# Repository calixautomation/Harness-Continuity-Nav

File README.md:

# LED Pattern Tester

A GUI application for testing wire connectivity on an 8x8 LED matrix. Uses a two-stage verification process: lock the wire in the slot, then verify connectivity by touching a metal plate.

## Quick Start

```bash
# Install dependencies
pip install -r harness_nav/requirements.txt

# Run the GUI (Desktop mode with test buttons)
cd HarnessNav
python harness_nav/scripts/run_desktop.py
```

## How It Works

```
┌─────────────────────────────────────────────────────────────┐
│                     LED Pattern Tester                       │
├──────────────┬──────────────────────────────────────────────┤
│              │                                              │
│  Pattern:    │    1   2   3   4   5   6   7   8            │
│  [Dropdown]  │                                              │
│              │    9  10  11  12  13  14  15  16            │
│  [Start]     │                                              │
│  [Reset]     │   17  18  19  20  21  22  23  24            │
│              │                                              │
│  [1. Lock]   │   25  26  27  28  29  30  31  32            │
│  [2. Verify] │                                              │
│              │   33  34  35  36  37  38  39  40            │
│  Progress:   │                                              │
│  ████░░ 50%  │   41  42  43  44  45  46  47  48            │
│              │                                              │
│  Current:    │   49  50  51  52  53  54  55  56            │
│  LED 4       │                                              │
│              │   57  58  59  60  61  62  63  64            │
│              │                                              │
└──────────────┴──────────────────────────────────────────────┘
```

### LED Colors

| Color | Meaning |
|-------|---------|
| Gray | Not part of pattern |
| Yellow | Needs to be tested |
| Cyan (blinking) | Currently active - waiting for wire |
| Orange | Wire locked in slot |
| Green | Verified/Passed |
| Red | Error/Wrong connection |

## Two-Stage Verification Workflow

```
1. Select Pattern    → LEDs in pattern turn YELLOW (pending)
2. Start Test        → First LED starts BLINKING (active)
3. Lock wire in slot → Limit switch triggers → LED turns ORANGE, beep (1500Hz)
4. Touch metal plate → Circuit completes → LED turns GREEN, beep (2500Hz)
5. Auto-advance      → Next LED starts blinking
6. Repeat            → Until all LEDs are GREEN
7. Complete          → Success message displayed
```

### Desktop Mode (Testing on PC)
- Use "1. Lock Wire" and "2. Verify Connection" buttons to simulate hardware
- Run with: `python harness_nav/scripts/run_desktop.py`

### Hardware Mode (Raspberry Pi)
- Buttons are hidden; uses SPI inputs
- Limit switch detects wire locked in slot
- Metal plate touch completes circuit for verification
- Run with: `python harness_nav/scripts/run_hardware.py`

## Creating Patterns

Use the built-in Pattern Editor (click "New Pattern") or edit `harness_nav/data/patterns.json`:

```json
{
    "patterns": [
        {
            "id": "pattern_1",
            "name": "Pattern 1",
            "description": "LEDs 3, 4, 8",
            "leds": [3, 4, 8]
        },
        {
            "id": "corners",
            "name": "Corner LEDs",
            "description": "All four corners",
            "leds": [1, 8, 57, 64]
        }
    ]
}
```

### LED Numbering

```
 1   2   3   4   5   6   7   8
 9  10  11  12  13  14  15  16
17  18  19  20  21  22  23  24
25  26  27  28  29  30  31  32
33  34  35  36  37  38  39  40
41  42  43  44  45  46  47  48
49  50  51  52  53  54  55  56
57  58  59  60  61  62  63  64
```

---

## Hardware Setup (Raspberry Pi)

### Required Components

| Component             | Description                               |
|-----------------------|-------------------------------------------|
| Raspberry Pi          | Main controller board                 |
| 10" Waveshare LCD     | Display for GUI (optional, can use HDMI)  |
| Limit Switch          | Detects when wire is locked in test slot  |
| Metal Plate           | Touch plate for connectivity verification |
| Piezo Buzzer          | Audio feedback (PWM driven)               |
| LEDs arranged in 8x8  | Physical LED display (optional)           |

### Wiring Diagram

```
Raspberry Pi 4B
       │
       ├── Pin 1 / 2 (3.3V / 5V) ──────── VCC (Pin 24 on TLC5925)
       │
       ├── Pin 6 / 9 (GND) ───────────── GND (Pin 12 on TLC5925)
       │
       ├── Pin 19 (GPIO 10 / MOSI) ───── SDI (Pin 23 on TLC5925)
       │
       ├── Pin 23 (GPIO 11 / SCLK) ───── CLK (Pin 22 on TLC5925)
       │
       ├── Pin 22 (GPIO 25) ──────────── LE (Pin 21 on TLC5925)
       │
       └── Pin 16 (GPIO 23) ──────────── \OE (Pin 10 on TLC5925, pulled LOW)
```

### Pin Connections

| Raspberry Pi Pin | TLC5925 Pin Name | TLC5925 Pin # | Notes                              |
|------------------|------------------|---------------|------------------------------------|
| Pin 1 / 2 (3.3V / 5V) | VCC              | Pin 24        | Logic power supply                |
| Pin 6 / 9 (GND)       | GND              | Pin 12        | Common ground                     |
| Pin 19 (GPIO 10 / MOSI)| SDI (Serial Data In) | Pin 23    | Data bus                          |
| Pin 23 (GPIO 11 / SCLK)| CLK (Clock)     | Pin 22        | Shift clock                       |
| Pin 22 (GPIO 25)       | LE (Latch Enable) | Pin 21      | Latches data into output          |
| Pin 16 (GPIO 23)       | \OE (Output Enable) | Pin 10   | Pull LOW (GND) to enable LED outputs |

### Circuit Notes

1. **Power Supply**: Connect the Raspberry Pi's 3.3V or 5V pin to the TLC5925's VCC (Pin 24). Ensure the voltage matches the logic level of the Raspberry Pi.

2. **Ground**: Connect the Raspberry Pi's GND pin to the TLC5925's GND (Pin 12).

3. **Serial Data Input (SDI)**: Connect GPIO 10 (MOSI, Pin 19) to the TLC5925's SDI (Pin 23).

4. **Clock (CLK)**: Connect GPIO 11 (SCLK, Pin 23) to the TLC5925's CLK (Pin 22).

5. **Latch Enable (LE)**: Connect GPIO 25 (Pin 22) to the TLC5925's LE (Pin 21). This pin latches the shifted data into the output.

6. **Output Enable (\OE)**: Connect GPIO 23 (Pin 16) to the TLC5925's \OE (Pin 10). Pull this pin LOW to enable the LED outputs.

---

## Deploy to Raspberry Pi 

### Option 1: Using Deployment Script (Windows)

```batch
cd HarnessNav\harness_nav\scripts
deploy_to_beaglebone.bat
```

Or specify IP address:
```batch
deploy_to_beaglebone.bat 192.168.7.2
```

### Option 2: Using Deployment Script (Linux/Mac)

```bash
cd HarnessNav/harness_nav/scripts
chmod +x deploy_to_beaglebone.sh
./deploy_to_beaglebone.sh
```

Or specify IP address:
```bash
./deploy_to_beaglebone.sh 192.168.7.2
```

### Option 3: Manual Deployment

```bash
# Copy files to BeagleBone
scp -r harness_nav debian@beaglebone.local:~/HarnessNav/

# SSH into BeagleBone
ssh debian@beaglebone.local

# Install dependencies
cd ~/HarnessNav
pip3 install -r harness_nav/requirements.txt

# Test run (hardware mode)
python3 harness_nav/scripts/run_hardware.py
```

### Enable Auto-Start on Boot

```bash
# SSH into BeagleBone
ssh debian@beaglebone.local

# Copy service file
sudo cp ~/HarnessNav/deploy/harness-nav.service /etc/systemd/system/

# Enable and start service
sudo systemctl daemon-reload
sudo systemctl enable harness-nav
sudo systemctl start harness-nav

# Check status
sudo systemctl status harness-nav

# View logs
journalctl -u harness-nav -f
```

### Disable Auto-Start

```bash
sudo systemctl stop harness-nav
sudo systemctl disable harness-nav
```

---

## Keyboard Shortcuts

| Key | Action |
|-----|--------|
| Escape | Exit application |
| Ctrl+Q | Exit application |
| F10 | Exit application (emergency) |

---

## Project Structure

```
HarnessNav/
├── README.md
├── PLAN.md                      # Project status and roadmap
├── deploy/
│   ├── harness-nav.service      # Systemd auto-start service
│   ├── install.sh               # Deployment installer
│   └── uninstall.sh             # Cleanup script
└── harness_nav/
    ├── requirements.txt
    ├── config/
    │   ├── settings.yaml        # Application settings
    │   ├── pins.yaml            # GPIO pin assignments
    │   └── led_layout.yaml      # LED panel configuration
    ├── data/
    │   └── patterns.json        # Test patterns
    ├── core/
    │   └── patterns/
    │       ├── models.py        # Data models
    │       └── pattern_loader.py
    ├── gui/
    │   ├── main_window.py       # Main application window
    │   ├── pattern_editor.py    # Pattern creation dialog
    │   └── widgets/
    │       └── grid_widget.py   # 8x8 LED grid with blinking
    ├── hal/
    │   ├── led_matrix/
    │   │   └── led_matrix.py    # LED matrix driver
    │   ├── switch/
    │   │   └── switch_handler.py # Dual switch handler
    │   └── buzzer/
    │       └── buzzer_driver.py  # PWM buzzer (lock/verify tones)
    └── scripts/
        ├── run_desktop.py        # PC testing mode
        ├── run_hardware.py       # BeagleBone hardware mode
        ├── deploy_to_beaglebone.sh
        └── deploy_to_beaglebone.bat
```

---

## Troubleshooting

### GUI won't start
```bash
pip install PyQt5 PyYAML
```

### No patterns in dropdown
Check that `harness_nav/data/patterns.json` exists and is valid JSON.

### Can't connect to BeagleBone
```bash
# Check if BeagleBone is reachable
ping beaglebone.local

# Try using IP address directly
ping 192.168.7.2   # USB connection
ping 192.168.1.x   # Network connection (check your router)
```

### GPIO not working on BeagleBone
```bash
# Install Adafruit library
pip3 install Adafruit-BBIO

# Check if running as correct user
# GPIO may need root or debian user in gpio group
sudo usermod -a -G gpio debian
```

### Buzzer not making sound
- Check PWM pin connection (P9_16)
- Verify buzzer polarity (+ to P9_16, - to GND)
- Test with: `python3 -c "from harness_nav.hal.buzzer import BuzzerDriver; b = BuzzerDriver('P9_16'); b.beep_verify()"`

### Application won't exit
- Press **Escape**, **Ctrl+Q**, or **F10**
- Or from SSH: `pkill -f run_hardware.py`

---

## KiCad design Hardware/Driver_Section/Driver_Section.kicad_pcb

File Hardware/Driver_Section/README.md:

# Driver Section — PCB Designs

KiCad projects for the two boards that make up the LED side of the harness
continuity tester (see the root [README.md](../../README.md) for the full
system). **Both boards have been fabricated, assembled, and verified working
on hardware.**

| Zip | Board | Role |
|---|---|---|
| `matrix_smd_v2_proj.zip` | **LED matrix board** | 8x8 SMD LED display the operator watches during a test |
| `tlc_carrier_proving_v8_with_parallel_RPi_breakout.zip` | **TLC5925 driver/carrier board** | Raspberry Pi hat that shifts data into 4x TLC5925 drivers and sinks the 64 LED channels |

Each zip is a full KiCad 10 project (schematic where applicable, PCB layout,
exported Gerbers/drill files, and a BOM) plus a VS Code `.history` folder
(auto-saved edit snapshots — safe to ignore/delete, not needed to build the
board).

---

## 1. `matrix_smd_v2` — LED Matrix Board

8x8 grid of SMD LEDs (64 total) that forms the visual pattern display
referenced throughout the main app (see `harness_nav/data/patterns.json` and
the LED numbering diagram in the root README).

- **Board size:** 132.1 x 95.3 mm, 2-layer FR4, 1.6 mm
- **PCB-only project** — no schematic capture, laid out directly in Pcbnew
- **LEDs:** D1–D64, footprint `LED_1206_3216Metric` (1206/3216 metric SMD LEDs)
- **Connectors:** two 2x32 IDC headers, 2.54 mm pitch
  - `JA` — row/anode side (A_2x32)
  - `JK` — column/cathode side (K_2x32)
  - Together these carry the row/column drive lines out to the TLC5925
    carrier board's 64-channel output header (J2)
- **Files:** `matrix_smd_v2.kicad_pcb`, `.kicad_pro`, `.kicad_prl`, BOM CSV,
  full Gerber/drill set in `matrix_smd_v2_gerber/` (also pre-zipped as
  `matrix_smd_v2_gerber.zip` for direct upload to a fab)

To re-order boards: send `matrix_smd_v2_gerber.zip` as-is to any 2-layer fab
(JLCPCB, PCBWay, PCB Power / LionCircuits in India, etc.) — no changes needed,
no special stackup.

---

## 2. `tlc_carrier` (rev C, "proving" variant) — TLC5925 Driver/Carrier Board

Raspberry Pi–mounted carrier board: 4x TLC5925 16-channel constant-current
LED sink drivers (64 channels total), driven over SPI-style shift
register signals from the Pi, plus headers for the limit switch and buzzer
used in the two-stage verification workflow.

- **Board size:** ~74.5 x 127 mm, 2-layer FR4, 1.6 mm, 1 oz copper
- **This is the "proving" build** (matches `BOM_tlc_proving.csv` and the
  physical PCB file): straight Pi-ribbon power, **no onboard USB-C input or
  buck-converter power stage**. `README_carrier.md` inside the zip documents
  a separate, more ambitious "full carrier" revision (USB-C power source,
  dual buck converters, screw-terminal power distribution) — that
  functionality is **not** present on the current `tlc_carrier.kicad_pcb` in
  this zip; treat that section of `README_carrier.md` as design notes for a
  future/alternate board, not as a description of what's built here.
- **J14 — parallel RPi breakout:** a second, unshrouded 2x20 header wired
  pin-for-pin with the main ribbon header (J1), so you can probe/jumper any
  Pi GPIO while the ribbon is connected. This is the "parallel RPi breakout"
  the zip is named for. Optional, can be left unpopulated.
- **Key connectors:**
  - `J1` — 2x20 IDC ribbon from the Pi GPIO header
  - `J14` — 2x20 plain header, parallel breakout of J1
  - `J2` — 2x32 header, 64 LED channel outputs → matrix board's `JA`/`JK`
  - `J9` — LCD power (PicoBlade 1.25 mm)
  - `J11`/`J12` — limit switch inputs (3V3 / GND / Signal, series-resistor
    protected)
  - `J13` — buzzer header (Signal/5V/GND)
  - `T1`/`J10` — 5V power in / LED power out screw terminals
- **LED current:** set by `R1–R4` (one R-EXT per TLC5925 bank),
  `I_OUT = (1.21V / R_EXT) x 18`. Proving build uses **2.2k → ~10 mA/channel**
  for yellow LEDs — change per-bank if a different LED color/current is
  needed.
- **Files:** `tlc_carrier.kicad_sch`, `.kicad_pcb`, `.kicad_pro`, `.kicad_prl`,
  two BOMs (`BOM_tlc_carrier.csv` = full/future carrier variant,
  `BOM_tlc_proving.csv` = **this** board), `DFM_NOTES.md` (revision history
  and fab/DRC notes), `README_carrier.md` (detailed bring-up and power notes —
  read the "proving" sections; ignore USB-C/buck-converter sections), full
  Gerber/drill set in `Gerbers/` (also pre-zipped as `Gerbers.zip`).

**Fab spec:** 2-layer FR4, 1.6 mm, 1 oz copper, HASL/ENIG, min track/space
0.25 mm, min via 0.6/0.3 mm — standard capability at JLCPCB/PCBWay/PCB
Power/LionCircuits, no special requests needed.

**Bring-up order:** populate the TLC5925s + decoupling first, verify 5V/3V3
rails before connecting the Pi, then connect the ribbon and run the LED
driver code (`harness_nav/hal/led_matrix/led_matrix.py`) to shift a test
pattern — see `DFM_NOTES.md` for the full checklist and known
schematic/PCB sync notes.

---

## How the two boards connect

```
Raspberry Pi
    │ (GPIO ribbon)
    ▼
tlc_carrier (J1) ──4x TLC5925──▶ J2 (2x32, 64 ch) ──cable──▶ JA/JK (2x32 x2)
    │                                                              │
    ├─ J11/J12 limit switch                                 matrix_smd_v2
    ├─ J13 buzzer                                            (8x8 LED grid)
    └─ J9 LCD power
```

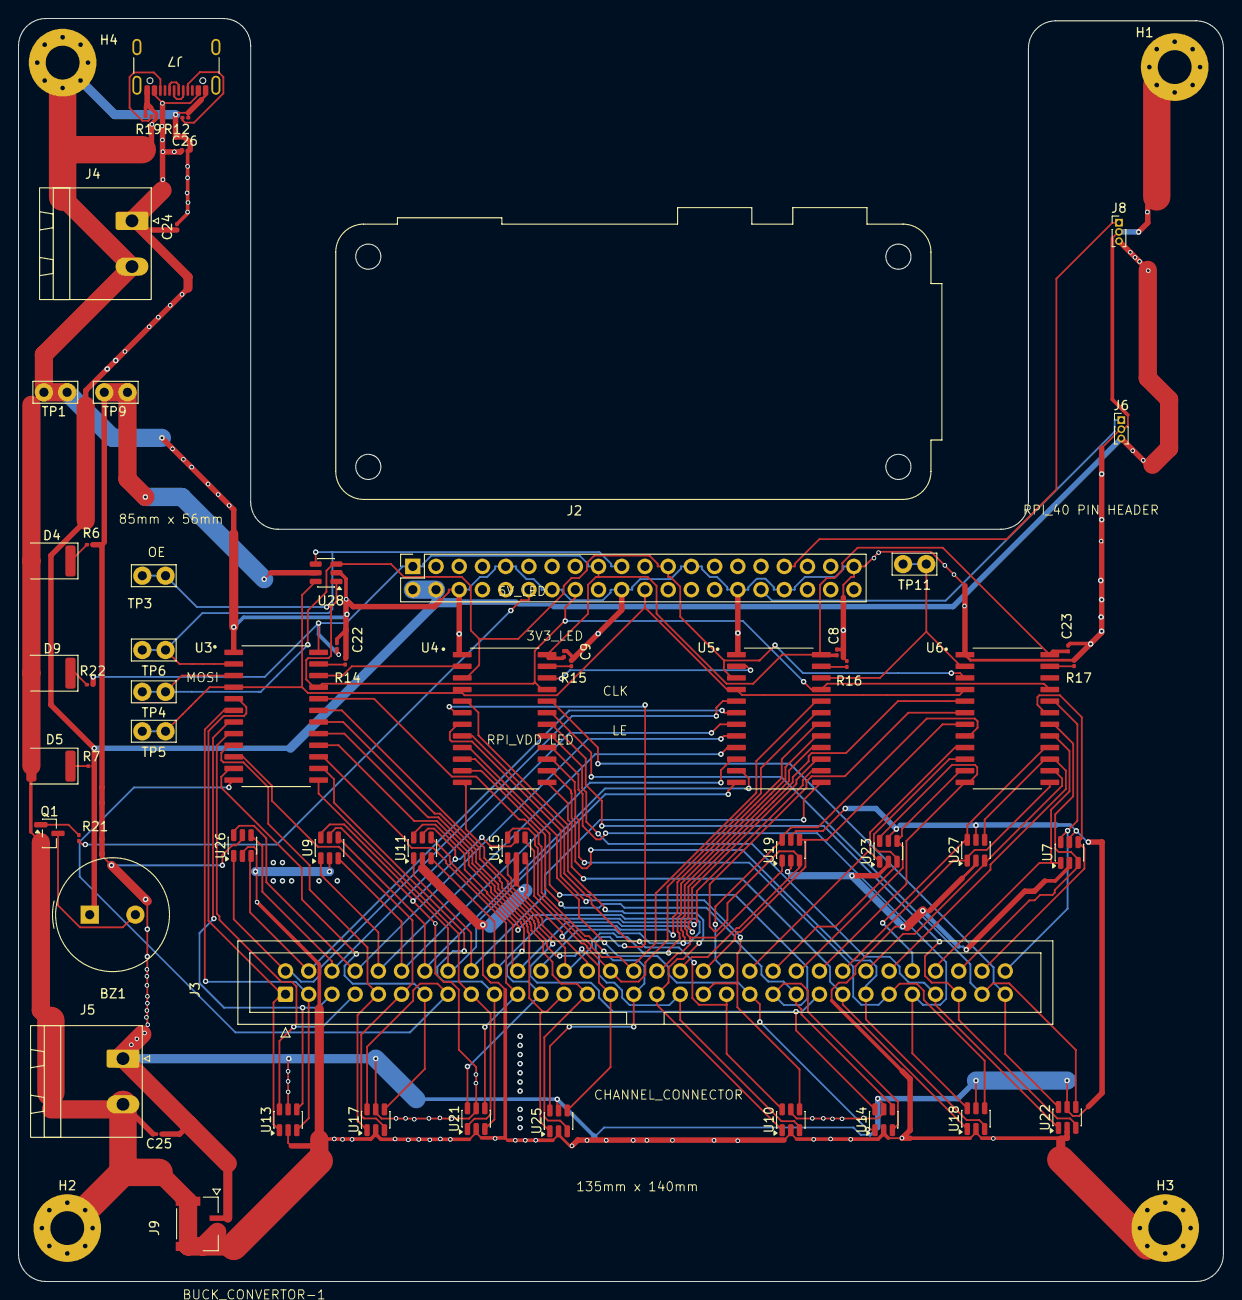
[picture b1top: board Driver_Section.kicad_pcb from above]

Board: 4 copper layers, 131.8 x 138.2 mm, 62 parts (0 on the bottom side), 91 nets.

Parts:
BZ1: Buzzer; Buzzer_TDK_PS1240P02BT_D12.2mm_H6.5mm
C8, C9, C22, C23, C24, C25, C26: 47u; C_0201_0603Metric
D4, D5, D9: LED; LED_1812_4532Metric
H1, H2, H3, H4: MountingHole_Pad; MountingHole_3.7mm_Pad_Via
J2: Raspberry_Pi_4; 3d_rpiheader
J3: Channel_Connector; IDC-Header_2x32_P2.54mm_Vertical
J4, J5: Screw_Terminal_01x02; PhoenixContact_MSTBA_2,5_2-G_1x02_P5.00mm_Horizontal
J6, J8: Conn_01x03_Pin; PinHeader_1x03_P1.00mm_Vertical
J7: USB_C_Receptacle_USB2.0_16P; USB_C_Receptacle_GCT_USB4105-xx-A_16P_TopMnt_Horizontal
J9: 5023860271; MOLEX_5023860271
Q1: MMBT2222A; SOT-23
R6: 330; R_0201_0603Metric
R7: 100; R_0201_0603Metric
R12, R19: 5k1; R_0201_0603Metric
R14, R15, R16, R17: 2K15; R_0201_0603Metric
R21: R; R_0201_0603Metric
R22: 22; R_0201_0603Metric
TP1, TP3, TP4, TP5, TP6, TP9, TP11: TestPoint; TestPoint_Bridge_Pitch2.54mm_Drill1.0mm
U3, U4, U5, U6: TLC5926IDWR; 3dtlc5926
U7, U9, U10, U11, U13, U14, U15, U17, U18, U19, U21, U22, U23, U25, U26, U27, U28: CDSOT236-0504C; SOT-23-6

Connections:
/3V3: C8.1, C9.1, C22.1, C23.1, J2.1 (3V3), J2.17 (3V3), R22.2, U3.24 (VDD), U4.24 (VDD), U5.24 (VDD), U6.24 (VDD)
/5V: C25.1, J5.1, J9.1, R6.2, TP9.1, U7.5 (VP), U9.5 (VP), U10.5 (VP), U11.5 (VP), U13.5 (VP), U14.5 (VP), U15.5 (VP), U17.5 (VP), U18.5 (VP), U19.5 (VP), U21.5 (VP), U22.5 (VP), U23.5 (VP), U25.5 (VP), U26.5 (VP), U27.5 (VP), U28.5 (VP)
/BUZZ: J2.12 (GPIO18/SPI1_~CE0/PCM_CLK/PWM0), R21.1
/CH_1: J3.1, U3.5 (OUT0), U13.1 (IO1)
/CH_2: J3.3, U3.6 (OUT1), U13.3 (IO2)
/CH_3: J3.5, U3.7 (OUT2), U13.4 (IO3)
/CH_4: J3.7, U3.8 (OUT3), U13.6 (IO4)
/CH_5: J3.9, U3.9 (OUT4), U17.1 (IO1)
/CH_6: J3.11, U3.10 (OUT5), U17.3 (IO2)
/CH_7: J3.13, U3.11 (OUT6), U17.4 (IO3)
/CH_8: J3.15, U3.12 (OUT7), U17.6 (IO4)
/CH_9: J3.17, U3.13 (OUT8), U21.1 (IO1)
/CH_10: J3.19, U3.14 (OUT9), U21.3 (IO2)
/CH_11: J3.21, U3.15 (OUT10), U21.4 (IO3)
/CH_12: J3.23, U3.16 (OUT11), U21.6 (IO4)
/CH_13: J3.25, U3.17 (OUT12), U25.1 (IO1)
/CH_14: J3.27, U3.18 (OUT13), U25.3 (IO2)
/CH_15: J3.29, U3.19 (OUT14), U25.4 (IO3)
/CH_16: J3.31, U3.20 (OUT15), U25.6 (IO4)
/CH_17: J3.33, U4.5 (OUT0), U10.1 (IO1)
/CH_18: J3.35, U4.6 (OUT1), U10.3 (IO2)
/CH_19: J3.37, U4.7 (OUT2), U10.4 (IO3)
/CH_20: J3.39, U4.8 (OUT3), U10.6 (IO4)
/CH_21: J3.41, U4.9 (OUT4), U14.1 (IO1)
/CH_22: J3.43, U4.10 (OUT5), U14.3 (IO2)
/CH_23: J3.45, U4.11 (OUT6), U14.4 (IO3)
/CH_24: J3.47, U4.12 (OUT7), U14.6 (IO4)
/CH_25: J3.49, U4.13 (OUT8), U18.1 (IO1)
/CH_26: J3.51, U4.14 (OUT9), U18.3 (IO2)
/CH_27: J3.53, U4.15 (OUT10), U18.4 (IO3)
/CH_28: J3.55, U4.16 (OUT11), U18.6 (IO4)
/CH_29: J3.57, U4.17 (OUT12), U22.1 (IO1)
/CH_30: J3.59, U4.18 (OUT13), U22.3 (IO2)
/CH_31: J3.61, U4.19 (OUT14), U22.4 (IO3)
/CH_32: J3.63, U4.20 (OUT15), U22.6 (IO4)
/CH_33: J3.2, U5.5 (OUT0), U26.1 (IO1)
/CH_34: J3.4, U5.6 (OUT1), U26.3 (IO2)
/CH_35: J3.6, U5.7 (OUT2), U26.4 (IO3)
/CH_36: J3.8, U5.8 (OUT3), U26.6 (IO4)
/CH_37: J3.10, U5.9 (OUT4), U9.1 (IO1)
/CH_38: J3.12, U5.10 (OUT5), U9.3 (IO2)
/CH_39: J3.14, U5.11 (OUT6), U9.4 (IO3)
/CH_40: J3.16, U5.12 (OUT7), U9.6 (IO4)
/CH_41: J3.18, U5.13 (OUT8), U11.1 (IO1)
/CH_42: J3.20, U5.14 (OUT9), U11.3 (IO2)
/CH_43: J3.22, U5.15 (OUT10), U11.4 (IO3)
/CH_44: J3.24, U5.16 (OUT11), U11.6 (IO4)
/CH_45: J3.26, U5.17 (OUT12), U15.1 (IO1)
/CH_46: J3.28, U5.18 (OUT13), U15.3 (IO2)
/CH_47: J3.30, U5.19 (OUT14), U15.4 (IO3)
/CH_48: J3.32, U5.20 (OUT15), U15.6 (IO4)
/CH_49: J3.34, U6.5 (OUT0), U19.1 (IO1)
/CH_50: J3.36, U6.6 (OUT1), U19.3 (IO2)
/CH_51: J3.38, U6.7 (OUT2), U19.4 (IO3)
/CH_52: J3.40, U6.8 (OUT3), U19.6 (IO4)
/CH_53: J3.42, U6.9 (OUT4), U23.1 (IO1)
/CH_54: J3.44, U6.10 (OUT5), U23.3 (IO2)
/CH_55: J3.46, U6.11 (OUT6), U23.4 (IO3)
/CH_56: J3.48, U6.12 (OUT7), U23.6 (IO4)
/CH_57: J3.50, U6.13 (OUT8), U27.1 (IO1)
/CH_58: J3.52, U6.14 (OUT9), U27.3 (IO2)
/CH_59: J3.54, U6.15 (OUT10), U27.4 (IO3)
/CH_60: J3.56, U6.16 (OUT11), U27.6 (IO4)
/CH_61: J3.58, U6.17 (OUT12), U7.1 (IO1)
/CH_62: J3.60, U6.18 (OUT13), U7.3 (IO2)
/CH_63: J3.62, U6.19 (OUT14), U7.4 (IO3)
/CH_64: J3.64, U6.20 (OUT15), U7.6 (IO4)
/CLK: J2.23 (SCLK_SPI0/GPIO11), TP4.1, U3.3 (CLK), U4.3 (CLK), U5.3 (CLK), U6.3 (CLK), U28.3 (IO2)
/GPIO_1: J2.32 (GPIO12/PWM0), J6.1
/GPIO_2: J2.33 (GPIO13/PWM1), J8.1
/LE: J2.22 (GPIO25/SDIO_DAT1), TP5.1, U3.4 (LE(ED1)), U4.4 (LE(ED1)), U5.4 (LE(ED1)), U6.4 (LE(ED1)), U28.6 (IO4)
/MOSI: J2.19 (MOSI_SPI0/GPIO10), TP6.1, U3.2 (SDI), U28.4 (IO3)
/RPI_VDD: BZ1.1 (+), C24.1, C26.1, J2.2 (5V), J2.4 (5V), J4.1, J6.3, J7.A4 (VBUS), J7.A9 (VBUS), J7.B4 (VBUS), J7.B9 (VBUS), J8.3, R7.2
/SDI: TP11.1, U5.22 (SDO), U6.2 (SDI)
/~OE: J2.16 (GPIO23/SDIO_CMD), TP3.1, U3.21 (~OE(ED2)), U4.21 (~OE(ED2)), U5.21 (~OE(ED2)), U6.21 (~OE(ED2)), U28.1 (IO1)
GND: C8.2, C9.2, C22.2, C23.2, C24.2, C25.2, C26.2, D4.2 (A), D5.2 (A), D9.2 (A), H1.1, H2.1, H3.1, H4.1, J2.6 (GND), J2.9 (GND), J2.14 (GND), J2.20 (GND), J2.25 (GND), J2.30 (GND), J2.34 (GND), J2.39 (GND), J4.2, J5.2, J6.2, J7.A1 (GND), J7.A12 (GND), J7.B1 (GND), J7.B12 (GND), J8.2, J9.2, J9.S1 (SHIELD1), J9.S2 (SHIELD2), Q1.2 (E), R12.2, R14.2, R15.2, R16.2, R17.2, R19.2, TP1.1, U3.1 (GND), U4.1 (GND), U5.1 (GND), U6.1 (GND), U7.2 (VN), U9.2 (VN), U10.2 (VN), U11.2 (VN), U13.2 (VN), U14.2 (VN), U15.2 (VN), U17.2 (VN), U18.2 (VN), U19.2 (VN), U21.2 (VN), U22.2 (VN), U23.2 (VN), U25.2 (VN), U26.2 (VN), U27.2 (VN), U28.2 (VN)
unnamed: BZ1.2 (-), Q1.3 (C)
unnamed: D4.1 (K), R6.1
unnamed: D5.1 (K), R7.1
unnamed: D9.1 (K), R22.1
unnamed: J7.A5 (CC1), R12.1
unnamed: J7.B5 (CC2), R19.1
unnamed: J7.A6 (D+), J7.B6 (D+)
unnamed: J7.A7 (D-), J7.B7 (D-)
unnamed: Q1.1 (B), R21.2
unnamed: R14.1, U3.23 (R-EXT)
unnamed: U3.22 (SDO), U4.2 (SDI)
unnamed: R15.1, U4.23 (R-EXT)
unnamed: U4.22 (SDO), U5.2 (SDI)
unnamed: R16.1, U5.23 (R-EXT)
unnamed: R17.1, U6.23 (R-EXT)

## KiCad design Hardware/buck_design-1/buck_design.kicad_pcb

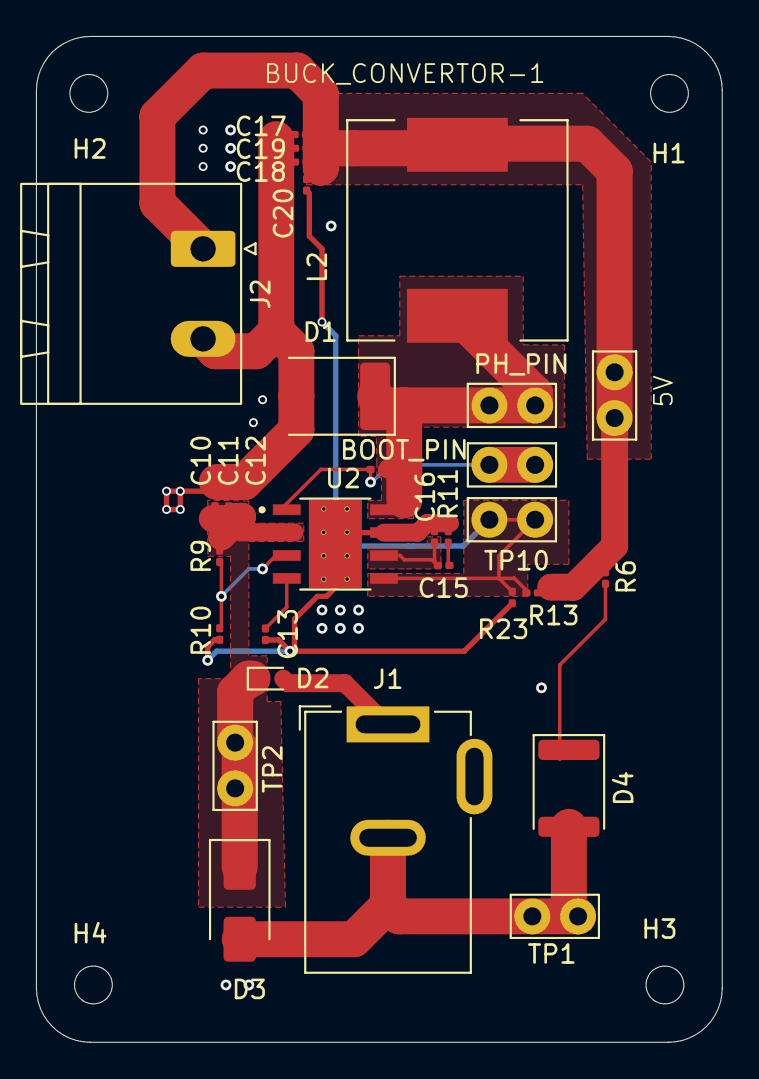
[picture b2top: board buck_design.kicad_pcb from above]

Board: 2 copper layers, 38.1 x 55.9 mm, 35 parts (0 on the bottom side), 12 nets.

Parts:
BOOT_PIN: TestPoint; TestPoint_Bridge_Pitch2.54mm_Drill1.0mm
C10, C11: 4.7uF; C_0201_0603Metric
C12, C13: 10nF; C_0201_0603Metric
C14: 0.1uF; C_0201_0603Metric
C15: 2200pF; C_0201_0603Metric
C16: 22pF; C_0201_0603Metric
C17, C18: 47uF; C_0201_0603Metric
C19, C20: 100nF; C_0201_0603Metric
D1: D; D_2114_3652Metric
D2: 1N4148WT; D_SOD-523
D3: SMAJ15A; D_SMA
D4: LED; LED_1812_4532Metric
H1, H2, H3, H4: MountingHole_Pad; MountingHole_2.1mm
J1: Barrel_Jack; BarrelJack_GCT_DCJ200-10-A_Horizontal
J2: Screw_Terminal_01x02; PhoenixContact_MSTBA_2,5_2-G_1x02_P5.00mm_Horizontal
L2: 4.7uH; L_Pulse_PA4320
PH_PIN: TestPoint; TestPoint_Bridge_Pitch2.54mm_Drill1.0mm
R6: 330; R_0201_0603Metric
R9: 665K; R_0201_0603Metric
R10: 130K; R_0201_0603Metric
R11: 37K4; R_0201_0603Metric
R13: 10K2; R_0201_0603Metric
R23: 1K96; R_0201_0603Metric
TP1, TP2, TP9, TP10: TestPoint; TestPoint_Bridge_Pitch2.54mm_Drill1.0mm
U2: TPS54531DDA; 3dmytps54531

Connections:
/5V: C17.1, C18.1, C19.1, C20.2, J2.1, L2.2, R6.2, R13.1, TP9.1
/Vin: C10.1, C11.1, C12.1, D2.1 (K), D3.1 (A1), R9.1, TP2.1, U2.2 (VIN)
GND: C10.2, C11.2, C12.2, C13.2, C16.2, C17.2, C18.2, C19.2, D1.2 (A), D3.2 (A2), D4.2 (A), J1.2, J2.2, R10.2, R11.2, R23.2, TP1.1, U2.7 (GND), U2.9 (EXP), U2.10 (EXP@1), U2.11 (EXP@2), U2.12 (EXP@3), U2.13 (EXP@4), U2.14 (EXP@5), U2.15 (EXP@6)
unnamed: C15.2, R11.1
unnamed: C14.2, D1.1 (K), L2.1, PH_PIN.1, U2.8 (PH)
unnamed: D2.2 (A), J1.1
unnamed: D4.1 (K), R6.1
unnamed: BOOT_PIN.1, C14.1, U2.1 (BOOT)
unnamed: C15.1, C16.1, U2.6 (COMP)
unnamed: R9.2, R10.1, U2.3 (EN)
unnamed: C13.1, U2.4 (SS)
unnamed: C20.1, R13.2, R23.1, TP10.1, U2.5 (VSENSE)

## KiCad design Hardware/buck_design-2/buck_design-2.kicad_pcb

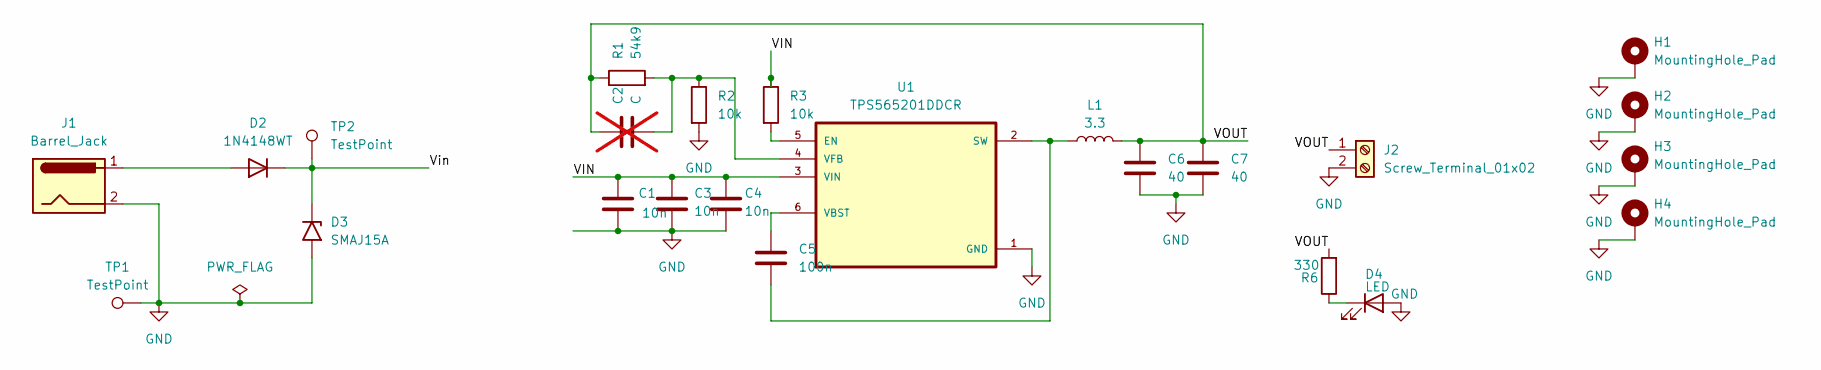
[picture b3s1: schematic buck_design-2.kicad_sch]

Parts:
C1, C3, C4: 10n; C_0201_0603Metric
C2: C; C_0201_0603Metric; not fitted
C5: 100n; C_0201_0603Metric
C6, C7: 40; C_0201_0603Metric
D2: 1N4148WT; D_SOD-523
D3: SMAJ15A; D_SMA
D4: LED; LED_1812_4532Metric
H1, H2, H3, H4: MountingHole_Pad; MountingHole_2.2mm_M2_DIN965_Pad
J1: Barrel_Jack; BarrelJack_GCT_DCJ200-10-A_Horizontal
J2: Screw_Terminal_01x02; PhoenixContact_MSTBA_2,5_2-G_1x02_P5.00mm_Horizontal
L1: 3.3; L_Pulse_PA4320
R1: 54k9; R_0201_0603Metric
R2, R3: 10k; R_0201_0603Metric
R6: 330; R_0201_0603Metric
TP1, TP2: TestPoint; TestPoint_Bridge_Pitch2.54mm_Drill1.0mm
U1: TPS565201DDCR; tps565201

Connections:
/VIN: C1.1, C3.1, C4.1, R3.1, U1.3 (VIN)
/VOUT: C2.1, C6.1, C7.1, J2.1, L1.2, R1.1, R6.2
/Vin: D2.1 (K), D3.1 (A1), TP2.1
GND: C1.2, C3.2, C4.2, C6.2, C7.2, D3.2 (A2), D4.2 (A), H1.1, H2.1, H3.1, H4.1, J1.2, J2.2, R2.2, TP1.1, U1.1 (GND)
unnamed: D2.2 (A), J1.1
unnamed: D4.1 (K), R6.1
unnamed: R3.2, U1.5 (EN)
unnamed: C5.2, L1.1, U1.2 (SW)
unnamed: C5.1, U1.6 (VBST)
unnamed: C2.2, R1.2, R2.1, U1.4 (VFB)

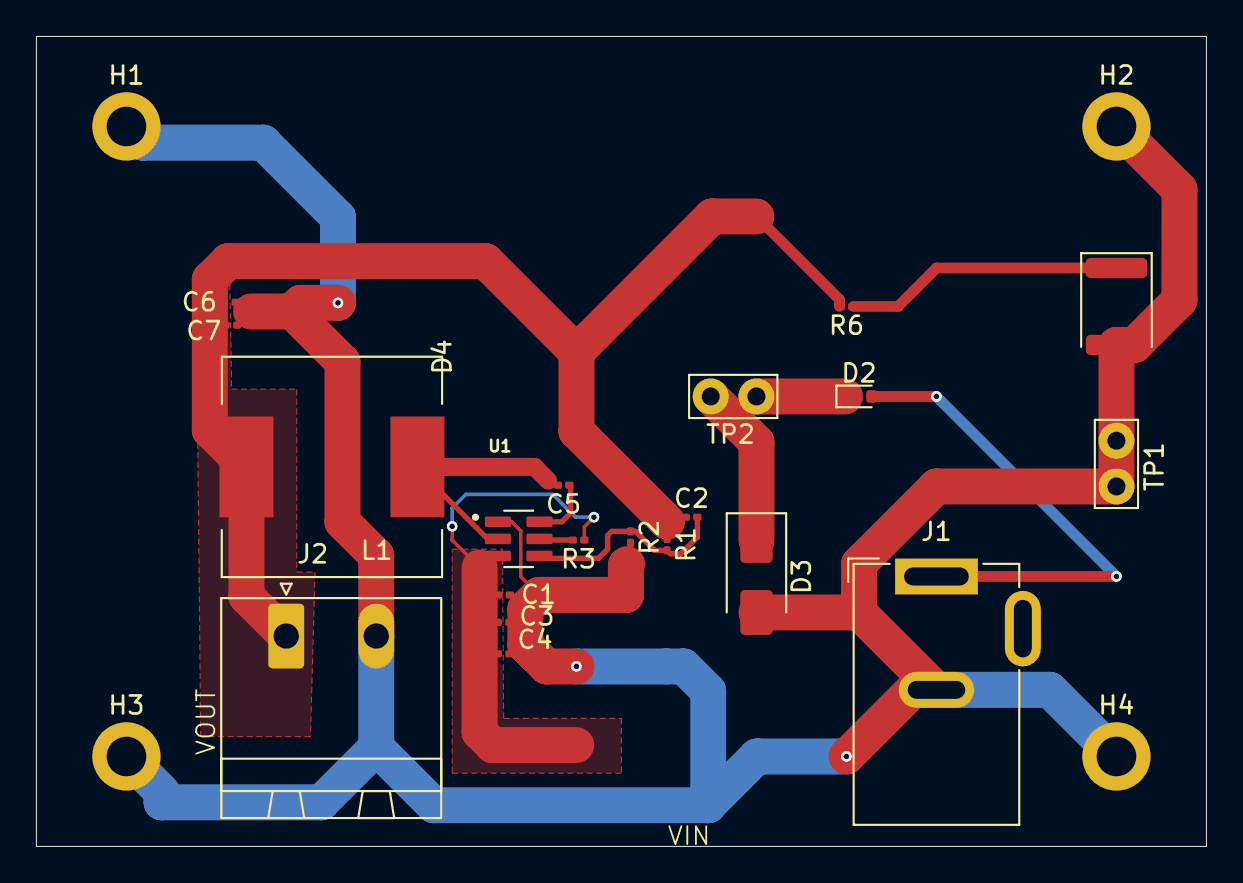
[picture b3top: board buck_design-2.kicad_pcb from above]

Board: 2 copper layers, 65.0 x 45.0 mm, 24 parts (0 on the bottom side), 10 nets.

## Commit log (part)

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2026-04-05 "Initial commit: LED Pattern Tester for wire harness testing
    - 8x8 LED grid with two-stage verification (lock + verify)
    - PyQt5 GUI with pattern editor
    - BeagleBone Black GPIO support
    - Desktop mode for PC testing"
2026-04-05 Create Affan_change1.py
    this is just a test file to check that if affan can make changes in this repo
2026-04-07 Added hello_rpi test file
2026-04-07 Updated RPi GPIO handling logic
2026-04-13 Create python-app.yml
    Add CI for tests
2026-04-16 Update python-app.yml
    Update with -m pytest flag
2026-04-16 Fixes to enable pytest
2026-04-16 Add README for adding tests
2026-04-21 your message
2026-04-26 Fix formatting issues in README.md
2026-05-01 added GUI files synced with dot matric display
2026-05-20 Fixes, enhancements, Working Hardware on Rpi
